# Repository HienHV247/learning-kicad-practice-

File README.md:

# KiCad Learning and Practice

Practice files and exercises created while learning KiCad through an online course.

These files are included to document my learning progress and are not presented as original independent designs.

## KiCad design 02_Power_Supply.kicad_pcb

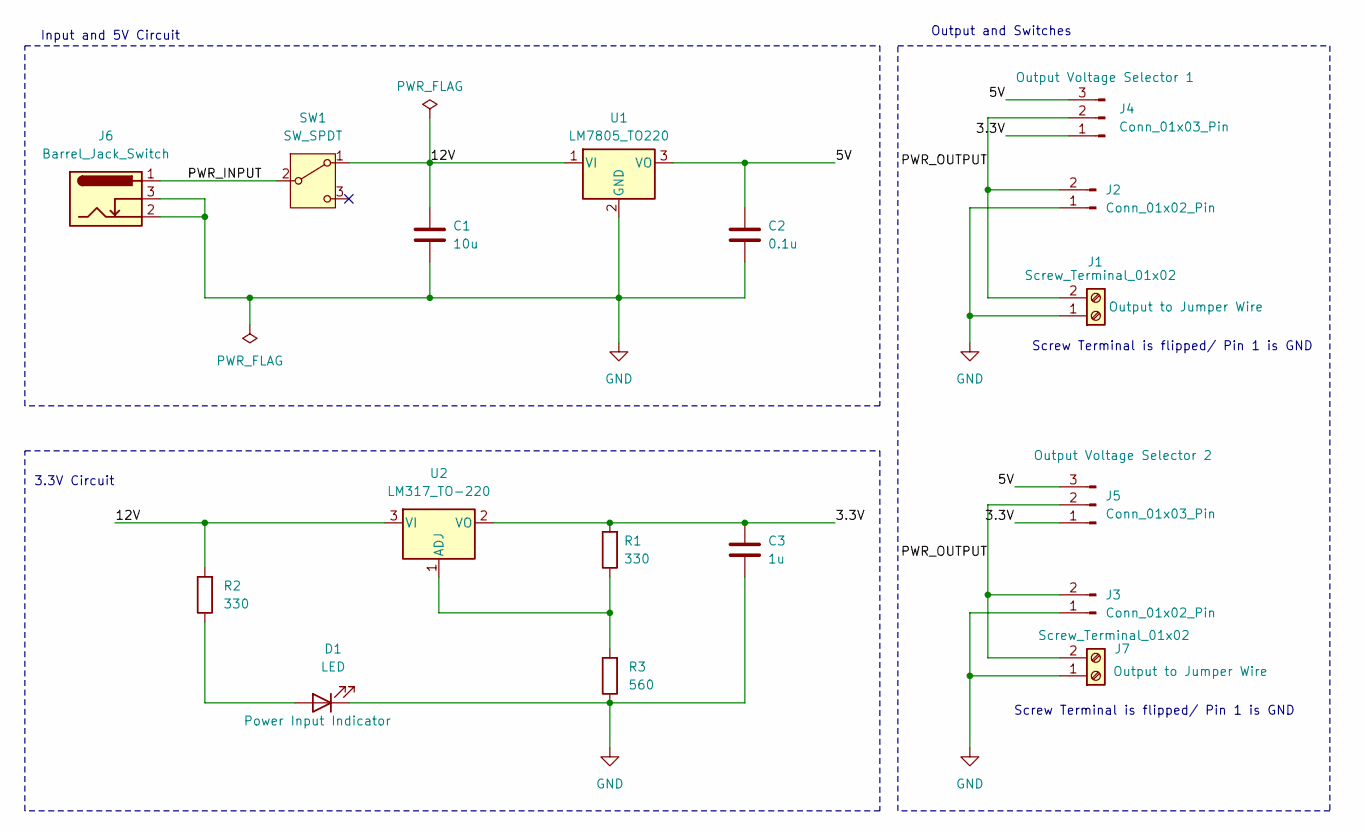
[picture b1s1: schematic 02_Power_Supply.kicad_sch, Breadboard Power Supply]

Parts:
C1: 10u; C_Disc_D3.0mm_W1.6mm_P2.50mm
C2: 0.1u; C_Disc_D3.0mm_W1.6mm_P2.50mm
C3: 1u; C_Disc_D3.0mm_W1.6mm_P2.50mm
D1: LED; LED_D5.0mm
J1, J7: Screw_Terminal_01x02; TerminalBlock_CUI_TB007-508-02_1x02_P5.08mm_Horizontal
J2, J3: Conn_01x02_Pin; PinHeader_1x02_P2.54mm_Vertical
J4, J5: Conn_01x03_Pin; PinHeader_1x03_P2.54mm_Vertical
J6: Barrel_Jack_Switch; BarrelJack_Horizontal
R1, R2: 330; R_Axial_DIN0204_L3.6mm_D1.6mm_P7.62mm_Horizontal
R3: 560; R_Axial_DIN0204_L3.6mm_D1.6mm_P7.62mm_Horizontal
SW1: SW_SPDT; SW_DPDT_CK_JS202011JCQN
U1: LM7805_TO220; TO-220-3_Vertical
U2: LM317_TO-220; TO-220-3_Vertical

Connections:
/3.3V: C3.2, J4.1, J5.1, R1.2, U2.2 (VO)
/5V: C2.1, J4.3, J5.3, U1.3 (VO)
/12V: C1.1, R2.2, SW1.1 (A), U1.1 (VI), U2.3 (VI)
/PWR_INPUT: J6.1, SW1.2 (B)
/PWR_OUTPUT: J1.2, J2.2, J3.2, J4.2, J5.2, J7.2
GND: C1.2, C2.2, C3.1, D1.1 (K), J1.1, J2.1, J3.1, J6.2, J6.3, J7.1, R3.1, U1.2 (GND)
unnamed: D1.2 (A), R2.1
unnamed: R1.1, R3.2, U2.1 (ADJ)

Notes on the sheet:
Output and Switches
Input and 5V Circuit
3.3V Circuit
Screw Terminal is flipped/ Pin 1 is GND

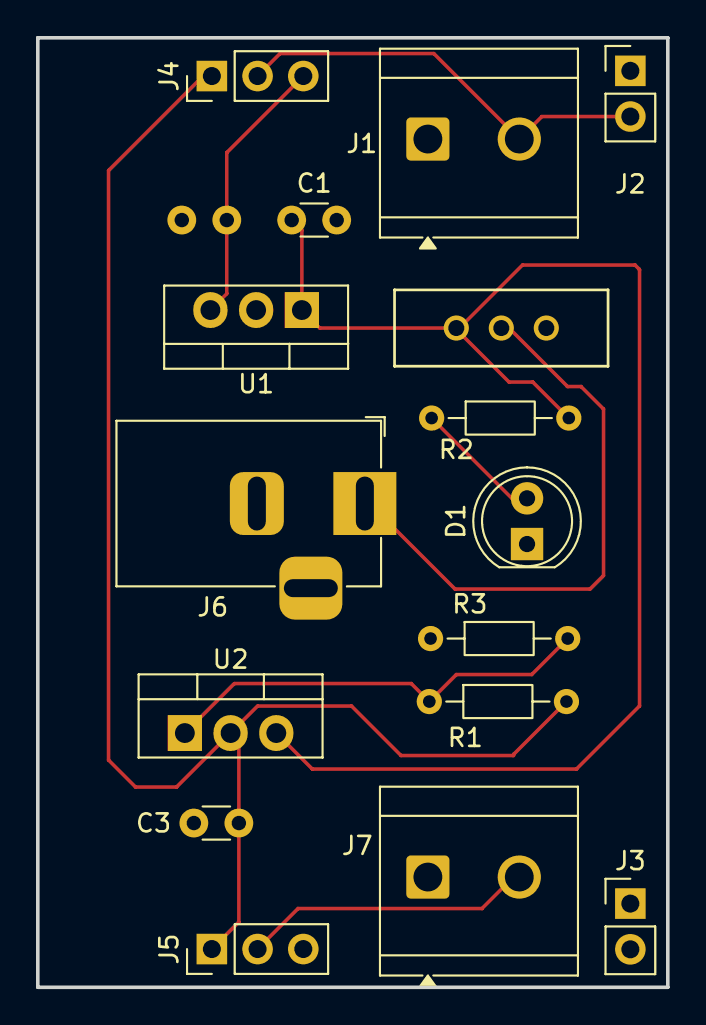
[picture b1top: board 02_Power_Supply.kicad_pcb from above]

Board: 2 copper layers, 35.0 x 52.8 mm, 17 parts (1 on the bottom side), 8 nets.

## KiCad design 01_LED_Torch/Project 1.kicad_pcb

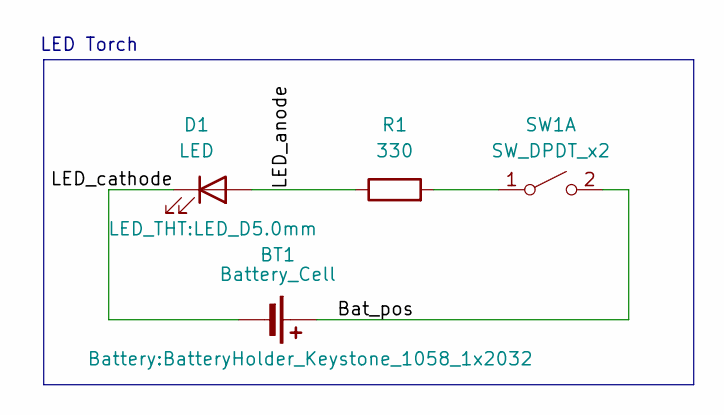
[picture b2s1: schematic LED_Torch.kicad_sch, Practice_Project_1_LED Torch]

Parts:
BT1: Battery_Cell; BatteryHolder_Keystone_1058_1x2032
D1: LED; LED_D5.0mm
R1: 330; R_Axial_DIN0204_L3.6mm_D1.6mm_P7.62mm_Horizontal
SW1: SW_DPDT_x2; SW_SPST_Omron_B3F-40xx

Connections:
/Bat_pos: BT1.1 (+), SW1.2 (B)
/LED_anode: D1.2 (A), R1.1
/LED_cathode: BT1.2 (-), D1.1 (K)
unnamed: R1.2, SW1.1 (A)

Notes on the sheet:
LED Torch

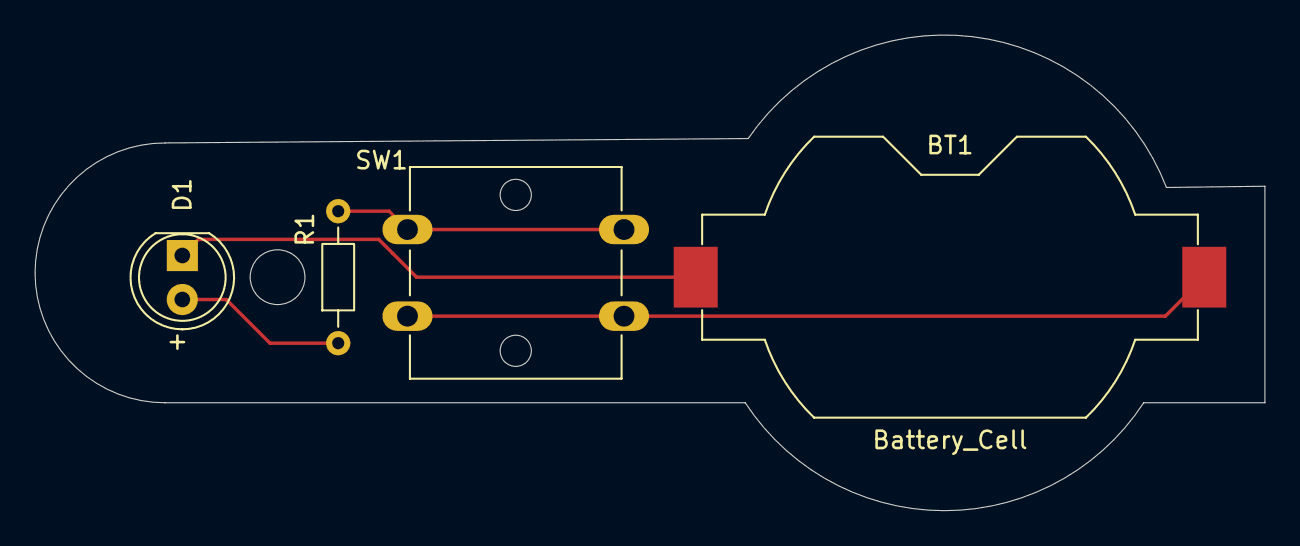
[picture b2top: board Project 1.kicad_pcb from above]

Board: 2 copper layers, 71.0 x 27.5 mm, 4 parts (0 on the bottom side), 4 nets.
